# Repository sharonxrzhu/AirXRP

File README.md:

# AirXRP

<br/>
<p align="center">
    
</p>

AirXRP is an educational quadcopter platform built around the SparkFun XRP Controller and Betaflight. The goal is to give students a simple Python interface for programming autonomous drone behaviors without requiring them to develop a flight-control system from scratch.

## Table of Contents
- [Prelude - Hardware](#prelude---hardware)
- [Chapter 1 - Preparation](#chapter-1---preparation)
  - [1.1 - Transmitter setup](#transmitter-setup)
  - [1.2 - Betaflight setup](#betaflight-setup)
  - [1.3 - XRP Files](#xrp-files)
  - [1.4 - OpenMV Camera setup](#openmv-camera-setup)
  - [1.5 - MSP Override Test](#msp-override-test)
  - [1.6 - Camera Axis Calibration](#camera-axis-calibration)
- [Chapter 2 - Functions to Use](#chapter-2---functions-to-use)
  - [2.1 - Drone API](#drone-api)
  - [2.2 - GPS](#gps)
- [Import Dependencies Diagram](#import-dependencies-diagram)
- [Debug](#debug)
  - [No response from msp override](#no-response-from-msp-override)
  - [Openmv camera not found at 0x42](#openmv-camera-not-found-at-0x42)
- [Developer Guide](#developer-guide)
  - [Order of RC Channels](#order-of-rc-channels)
  - [MSP Override Mask Channels](#msp-override-mask-channels)

## Prelude - Hardware
Before starting on this software guide, make sure to follow: https://www.printables.com/model/1707431-airxrp-alpha-xrp-powered-3d-printed-quadcopter for the hardware assembly of the AirXRP.

## Chapter 1 - Preparation

### Transmitter setup
Turn on the transmitter

1. long hold "OK" button until you see MENU screen
2. click "OK" to go into SYSTEM screen
3. click "DOWN" until reaching "Aux switches", click "OK"
4. Turn all switches On by clicking "UP" and "OK" to move to the next switch, when reaches "Ch", click "UP" until Ch:10. **Long hold "Cancel" button to save everything**
5. Click "Cancel" to go back to MENU, and click "UP" and "OK" to go into FUNCTIONS screen
6. Click "DOWN" until reaching "Aux, channels", click "OK"
7. Click "OK" until reaching Channel 7, while arrows are point at Channel 7 and Source, click "DOWN" until Source is SwA, click "OK". Repeat for Channel 8, 9 and 10, each corresponding to SwB, SwC, SwD, respectively. **Long hold "Cancel" button to save everything**

This sets the switches from left to right, to AUX3, 4, 5, and 6, the left spin knob to AUX1, and right spin knob to AUX2, in betaflight.

### Betaflight setup
Open Betaflight app https://app.betaflight.com/ and connect to the flight controller through the on board usb-c port

1. In Sensors tab, change Pitch degrees from 0 to 180 under Board Alignment. Click Calibrate. 
2. In Ports tab, enable Configuration/MSP for UART4 and Serial RX for UART7, click Save and Reboot in the lower right hand side corner.
3. In Receiver tab, for serial receiver provider, change CRSF to IBUS, click Save in the lower right hand side corner.

Checkpoint: Turning on the transmitter and the drone, you should see roll, pitch, yaw, throttle, and the auxiliary channels change when moving the sticks and switches on your transmitter.

4. In CLI tab, type in "set msp_override_channels_mask = [number]" where [number] is what controls you would like the xrp to control when in msp override mode. Default full control of roll, pitch, throttle, and yaw is 15. For more information on what number to use, check out [Developer Guide](#developer-guide).
5. In modes tab, enable ARM with an AUX and Min Max of your choice, enable ANGLE if you would like to fly in ANGLE mode, and after setting a number for msp_override_channels_mask, enable MSP OVERRIDE with an AUX and MIN MAX of your choice. 
6. In PID Tuning, change Motor Output Limit from 100 to 66.
7. In Motors Tab, click on Reorder motors and then motor direction and follow the instructions to setup motors. Make sure to plug in the battery for the motors to run.

Checkpoint: The drone should now be capable of manual flying.

### XRP Files

Make sure your XRP contains
- airxrp_openmv_axis_calibrate.py
- fc.py
- gps.py
- hover.py
- msp.py
- msp_test.py

### OpenMV Camera setup

Download OpenMV IDE: https://openmv.io/pages/download?srsltid=AfmBOoorWgGWSutgBUVmrJHAUmXsZcqh9ppmNFL8Xp0shk191VoGpuC1

Save mavlink_opticalflow_openmw_ide.py to main by
1. connect OpenMV camera to the OpenMV camera ide through on board usb-c port
2. go to file explorer and look for OpenMV camera disk
3. open OpenMV camera disk and open the file "main"
4. copy mavlink_opticalflow_openmw_ide.py into the file "main" and save the file

### MSP Override Test
XRP controls the drone through Betaflight MSP Override. This communication happens through msp.py. We want to make sure the drone is setup properly to communicate between the XRP the flight controller.

**Run msp_test.py** 

If you receive: 
"SUCCESS: MSP communication working both ways" 
This means your hardware setup is correct and ready to go

If you receive:
"No response"
Check out [Debug](#debug)

### Camera Axis Calibration
The OpenMV may be mounted in different orientations, so AirXRP does not assume camera X/Y correspond directly to aircraft roll/pitch.
Before hover() is used, **run airxrp_openmv_axis_calibrate.py**

The calibration procedure is:
Hold the drone level and still.
Move the entire aircraft approximately 10–20 cm to its physical right.
Return it and hold still.
Move the aircraft approximately 10–20 cm forward.
Keep the aircraft level and avoid yawing it.
The script determines the transformation from camera coordinates into aircraft body coordinates and writes:
/openmv_axis_calibration.txt 

> :exclamation: **Make sure /openmv_axis_calibration.txt is saved in the XRP before running hover()**

The calibration only needs to be repeated if the camera mounting orientation changes.

## Chapter 2 - Functions to Use

Create a new file (ex: student.py) as the main file to work with.

### Drone API
The Drone class provides the student-facing interface. It can be found in fc.py.
Current movement functions include:
- move_forward()
- move_backward()
- move_left()
- move_right()
- hover() (with manual control of throttle)

Example:
```python
from fc import Drone

drone = Drone()

# Pilot manually raises the drone to the desired altitude.

# Hold the drone's horizontal X/Y position for 5 seconds.
# Pilot continues controlling throttle.
drone.hover(duration=5)

# Move forward for 1 second.
drone.move_forward(speed=0.3, duration=1)

# Hold horizontal position again.
drone.hover(duration=5)
```

### GPS
AirXRP also supports a GPS module using gps.py

GPS is intended primarily for larger-scale position and waypoint behaviors, while OpenMV optical flow provides faster local motion correction near the ground.

GPS is not very accurate in the z direction, but relatively accurate in the x and y direction, with drifting that happens overtime.

Current GPS functions include:
- get_location() — returns latitude, longitude, and altitude
- set_origin() — saves the current GPS location as x = 0, y = 0, z = 0
- get_xyz() — returns position in meters relative to the saved origin

Example:
```python
from gps import AirXRPGPS

gps = AirXRPGPS()

gps.set_origin()

while True:
    position = gps.get_xyz()

    if position:
        print("X:", position["x"], "m")
        print("Y:", position["y"], "m")
        print("Z:", position["z"], "m")
    else:
        print("No GPS position")
```
where 
- +x = East
- +y = North
- +z = Up

## Import Dependencies Diagram

```mermaid
flowchart TD
    Student["student.py"]
    FC["fc.py"]
    GPS["gps.py"]
    Hover["hover.py"]
    MSP["msp.py"]

    Student --> FC
    Student --> GPS
    FC --> Hover
    Hover --> MSP
    GPS --> MSP
```

## Debug

### no response from msp override

- Make sure flight controller is powered on
- Make sure UART4 in Betaflight is enabled for Configuration/MSP
- Unplug and replug in wire from xrp to flight controller, make sure all wires are connected. Often times it is a physical connection problem

### openmv camera not found at 0x42

- plug usb-c cable into openmv camera port for a few seconds and plug ucb-c cable back into xrp. This should reset the code in the openmv camera for it to run again.

## Developer Guide

### Order of RC Channels

Betaflight uses RC channel mapping of AETR1234 order

- A = Aileron = Roll
- E = Elevator = Pitch
- T = Throttle
- R = Rudder = Yaw
- 1 = AUX1
- 2 = AUX2
- 3 = AUX3
- 4 = AUX4
... (continues on to AUX5 and AUX6 but just not included in the name)

So when sending raw RC values to Betaflight with MSP_SET_RAW_RC, the values should be sent in this order:

```python
[
    roll,
    pitch,
    throttle,
    yaw,
    aux1,
    aux2,
    aux3,
    aux4,
]
```

> :exclamation: One important distinction is that this raw AETR1234 order does not necessarily match the order returned by MSP_RC. In the current AirXRP setup, MSP_RC is read in Betaflight's logical order:

Roll, Pitch, Yaw, Throttle, AUX1, AUX2, AUX3, ...

So for example:

rc[3] is the throttle value when reading MSP_RC, even though throttle is the third channel when sending MSP_SET_RAW_RC.

### MSP Override Mask Channels

msp_override_channels_mask tells Betaflight which RC channels are allowed to be replaced by MSP commands when MSP Override mode is active.

Each channel corresponds to one bit:

| Bit | Value | Channel in AETR1234 raw order |
|---:|---:|---|
| 0 | 1 | Roll / Aileron |
| 1 | 2 | Pitch / Elevator |
| 2 | 4 | Throttle |
| 3 | 8 | Yaw / Rudder |
| 4 | 16 | AUX1 |
| 5 | 32 | AUX2 |
| 6 | 64 | AUX3 |
| 7 | 128 | AUX4 |

To override multiple channels, add the corresponding values together.

For example:

- 1 = Roll only
- 2 = Pitch only
- 3 = Roll + Pitch
- 4 = Throttle only
- 7 = Roll + Pitch + Throttle
- 8 = Yaw only
- 11 = Roll + Pitch + Yaw
- 15 = Roll + Pitch + Throttle + Yaw

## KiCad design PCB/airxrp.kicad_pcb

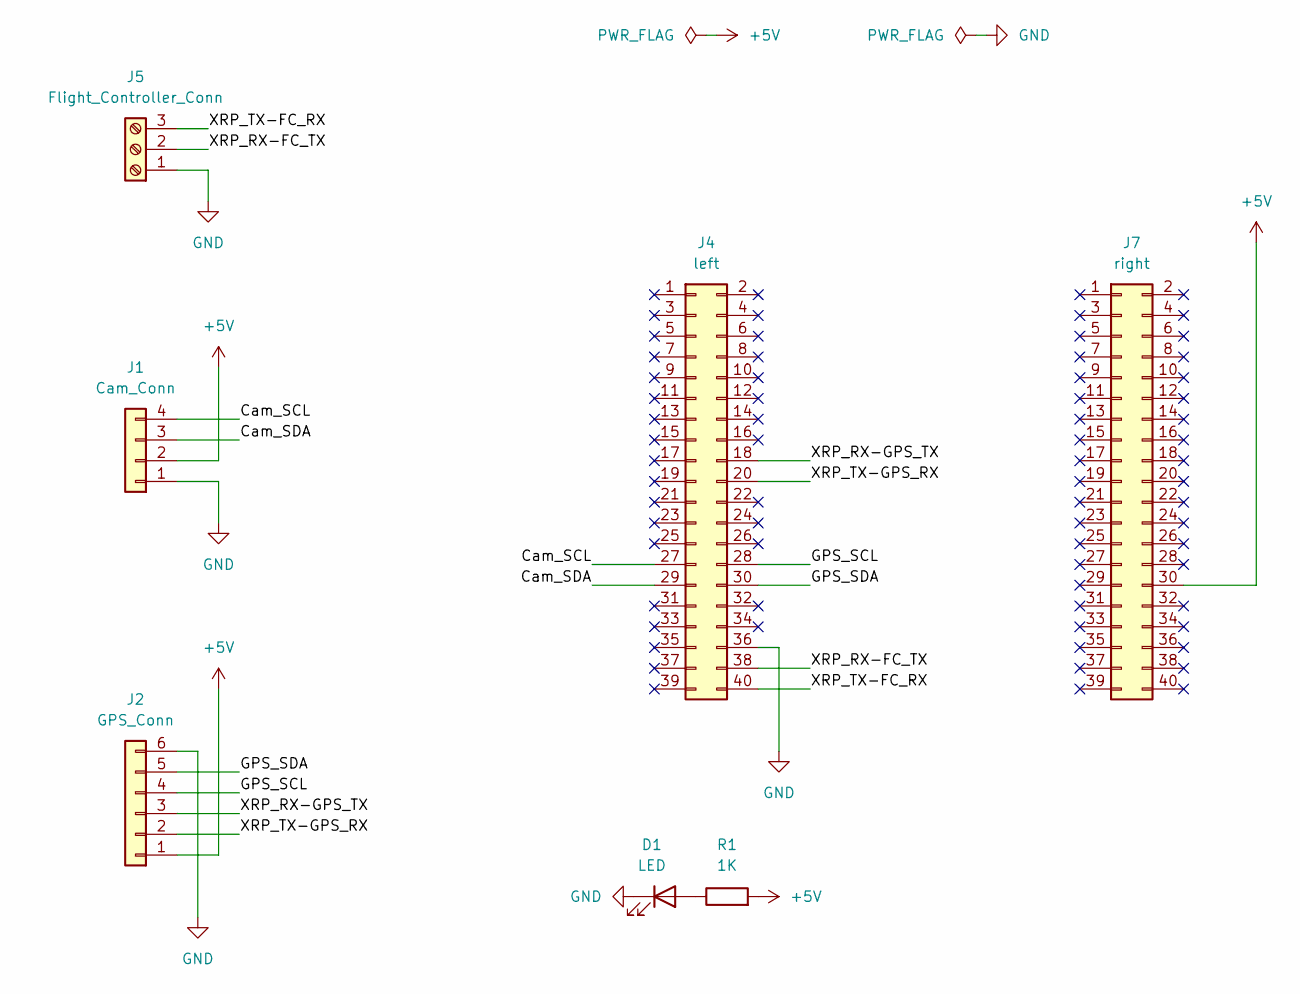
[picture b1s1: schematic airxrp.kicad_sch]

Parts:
D1: LED; LED_0603_1608Metric
J1: Cam_Conn; TerminalBlock_Phoenix_MPT-0,5-4-2.54_1x04_P2.54mm_Horizontal
J2: GPS_Conn; JST_GH_SM06B-GHS-TB_1x06-1MP_P1.25mm_Horizontal
J4: left; PinHeader_2x20_P2.54mm_Vertical
J5: Flight_Controller_Conn; TerminalBlock_Phoenix_MPT-0,5-3-2.54_1x03_P2.54mm_Horizontal
J7: right; PinHeader_2x20_P2.54mm_Vertical
R1: 1K; R_0603_1608Metric

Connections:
+5V: J1.2, J2.1, J7.30 (Pin_30_30), R1.2
/Cam_SCL: J1.4, J4.27
/Cam_SDA: J1.3, J4.29
/GPS_SCL: J2.4, J4.28
/GPS_SDA: J2.5, J4.30
/XRP_RX-FC_TX: J4.38, J5.2
/XRP_RX-GPS_TX: J2.3, J4.18
/XRP_TX-FC_RX: J4.40, J5.3
/XRP_TX-GPS_RX: J2.2, J4.20
GND: D1.1 (K), J1.1, J2.6, J4.36, J5.1
unnamed: D1.2 (A), R1.1

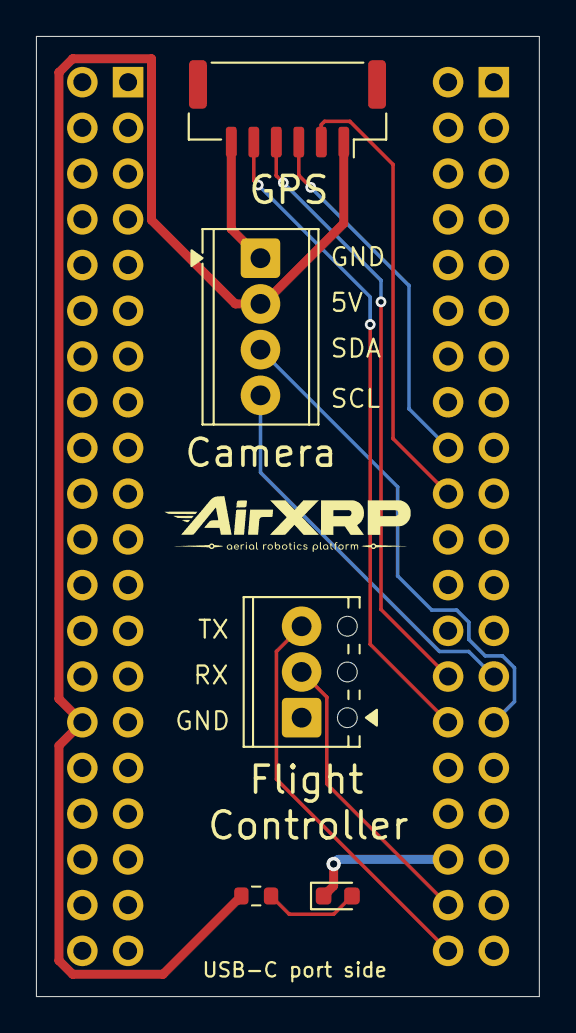
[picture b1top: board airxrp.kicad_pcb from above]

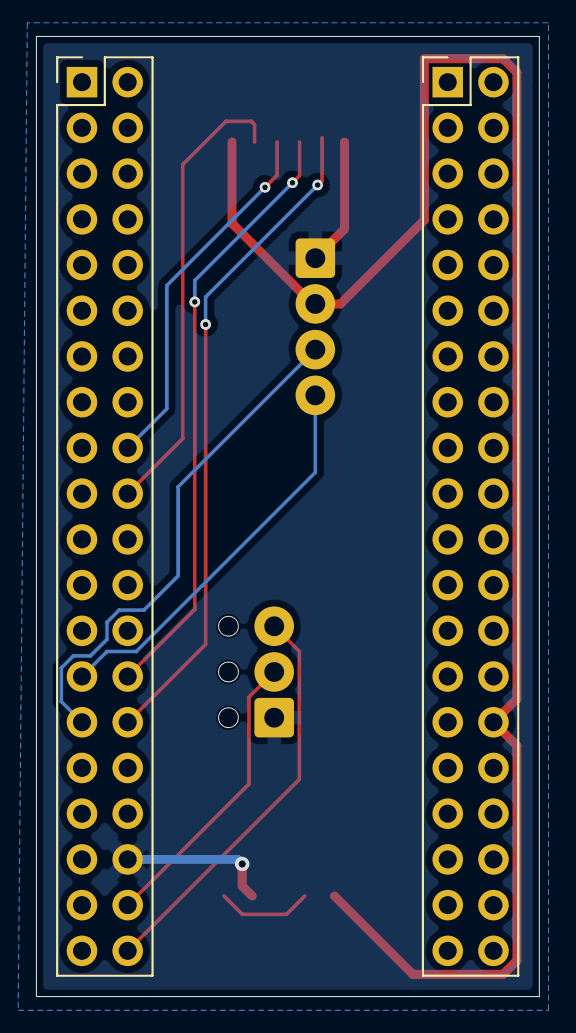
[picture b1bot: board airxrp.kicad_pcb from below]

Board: 2 copper layers, 27.9 x 53.3 mm, 7 parts (2 on the bottom side), 11 nets.

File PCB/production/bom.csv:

Designator	Footprint	Quantity	Value
D1	603	1	LED
J1	"TerminalBlock_Phoenix_MPT-0,5-4-2.54_1x04_P2.54mm_Horizontal"	1	Cam_Conn
J2	JST_GH_SM06B-GHS-TB_1x06-1MP_P1.25mm_Horizontal	1	GPS_Conn
J4	PinHeader_2x20_P2.54mm_Vertical	1	left
J5	"TerminalBlock_Phoenix_MPT-0,5-3-2.54_1x03_P2.54mm_Horizontal"	1	Flight_Controller_Conn
J7	PinHeader_2x20_P2.54mm_Vertical	1	right
R1	603	1	1K

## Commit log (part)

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2026-06-22 added student.py
    Implement drone mission control using AUX3 trigger.
2026-06-22 Added fc.py
    flight controller libraries
2026-06-22 Add MSP class for Betaflight communication
2026-06-22 Add AirXRPGPS class to read and process GPS data
    Implement AirXRPGPS class for GPS data handling
